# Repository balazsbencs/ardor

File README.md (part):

<h1 align="center">
  
</h1>

Ardor is a standalone Raspberry Pi guitar-processing platform with a realtime
audio engine, touchscreen/footswitch UI, preset storage, a browser-based manager
served by the device, and a reproducible Buildroot firmware image.

The signal chain supports Neural Amp Modeler `.nam` files, cabinet impulse
responses, 35 hosted modulation/delay/reverb effects, compression, noise
gating, five-band parametric EQ with high-pass and low-pass filters, global gain,
and a safety limiter. The same
LVGL interface runs in the SDL desktop simulator and on the Raspberry Pi Touch
Display 2.

Presets support serial chains, Dual Rig's separate left and right paths, and
Wet/Dry/Wet routing with a mono amp lane mixed alongside a stereo effects lane.

The pedal is an appliance rather than a plugin host. Plugin formats and an OTA
update workflow are outside the current scope.

<table>
  <tr>
    <td width="50%"></td>
    <td width="50%"></td>
  </tr>
  <tr>
    <td align="center"><sub>Build the chain from neural amps, cabs and effects</sub></td>
    <td align="center"><sub>Four-track looper on the footswitches</sub></td>
  </tr>
</table>

## What You Need

To build an Ardor pedal, start with a Raspberry Pi 4 (the 1 GB model is
enough), its USB-C power supply, and a microSD card for the Ardor image. Put
the Raspberry Pi Codec Zero audio board on top of the Pi, and connect the 5 inch
Raspberry Pi Touch Display 2 with its ribbon cable. A guitar cannot connect
directly to the Codec Zero, so you also need the small Ardor guitar input buffer
board. You can order it from JLCPCB with the parts already fitted (see
[Guitar Input Buffer](#guitar-input-buffer)), and it runs from a normal 9 V
guitar pedal power supply. For a complete floor pedal, add four momentary
footswitches, one rotary knob (encoder) for the master volume, one 1/4 inch
input jack, two 1/4 inch output jacks, and a case. You can 3D print the case
from [`enclosure.openscad`](enclosure.openscad). You need a soldering iron for
some basic soldering of the jacks, switches, and wires. MIDI and expression
pedal inputs come later. The [hardware assembly guide](docs/hardware-assembly.md)
shows all the wiring.

## Community

See [CONTRIBUTING.md](CONTRIBUTING.md) before proposing changes. Contributors
are recognized in [CONTRIBUTORS.md](CONTRIBUTORS.md), and suspected
vulnerabilities should be reported privately according to
[SECURITY.md](SECURITY.md).

## Requirements

- CMake 3.20+
- C++20 compiler
- Single-precision FFTW development files (`libfftw3-dev` on Debian/Ubuntu,
  `brew install fftw` on macOS). Custom SDK paths can be supplied through
  `ARDOR_FFTW_INCLUDE_DIR` and `ARDOR_FFTW_LIBRARY` at CMake configure.
- Git access during CMake configure, for `miniaudio` and `NeuralAmpModelerCore`
- SDL2 for the LVGL desktop simulator (`ARDOR_UI_BACKEND=sdl`)
- macOS for desktop testing, or Linux for target-style builds
- Optional: Go for the manager daemon, Node.js 24 via `nvm use` for the manager
  web app, and Docker for the Buildroot firmware image
- Local test assets:
  - `models/test.nam`
  - `irs/test.wav`
  - optional `reverb-irs/test.wav`
  - optional dry input WAV for offline rendering

Real `.nam` and IR files are ignored by git. Keep licensed/user-provided assets local unless redistribution is allowed.

The POG3 DSP links FFTW, which is GPL-2.0-or-later. Distribution of FFTW-linked
binaries must comply with that license; the repository's MIT license does not
cover FFTW. See [the FFT backend notes](docs/pog3-fft-backend-evaluation.md).

## Guitar Input Buffer

A passive guitar must pass through the Ardor input buffer before it reaches
the Codec Zero. The repository contains the separate, minimal KiCad project
in [`buffer/`](buffer/).

You can order a board with the SMD parts fitted through
[JLCPCB](https://jlcpcb.com/). Upload these files from
[`buffer/jlcpcb/production_files/`](buffer/jlcpcb/production_files/):

- [`GERBER-buffer.zip`](buffer/jlcpcb/production_files/GERBER-buffer.zip) for the PCB files.
- [`BOM-buffer.csv`](buffer/jlcpcb/production_files/BOM-buffer.csv) for the parts list.
- [`CPL-buffer.csv`](buffer/jlcpcb/production_files/CPL-buffer.csv) for the part placement list.

The production files do not include audio jacks, wires, connectors, or the
enclosure. Add these parts after the board arrives. Connect the guitar jack to
`GUITAR_IN` and connect `GUITAR_OUT` to the Codec Zero input. Follow the buffer
schematic for power and ground connections.

## Preset Storage

Preset files live under the data root in bank/slot folders, for example:

- `presets/bank-000/preset-0.json`

Block assets inside preset JSON stay relative to that same data root, such as `models/clean.nam`, `irs/open-back.wav`, or `reverb-irs/small-room.wav`. Cabinet IRs and convolution reverb IRs use separate directories. Existing convolution presets that reference an installed `irs/` asset remain compatible, while new reverb selections use `reverb-irs/`. Absolute paths and `..` traversal are rejected. Real `.nam` models and IRs stay local and are not committed unless redistribution is allowed.

Convolution reverb exposes **Reverb time** in the pedal and manager editors.
It scales the recorded decay from 25% to 100%; 100% preserves the original IR.
For example, a two-second decay becomes approximately one second at 50%.
The processor estimates RT60 from the loaded stereo IR and applies a decay
envelope without changing reflection timing, pitch, or embedded pre-delay.
IRs shorter than 100 ms, silent impulses, and responses without a reliable
decay estimate stay unchanged. The four-second IR cap still applies.
Live edits crossfade using the existing convolution history. This control is
shared across scenes; convolution-kernel preparation runs on the control thread.

### Scenes

Version-4 presets contain four named scenes. A scene changes prepared parameter
values, qualified effect bypass states, input gain, WDW lane values, and a
post-rig trim without rebuilding the audio engine. Each scene can switch
instantly or transition over 0.1–10 seconds.

On a scene-enabled preset, hold FS3 + FS4 for 600 ms to enter or leave the
Scenes layer. The four footswitches then recall the four scene plates. Hold
FS1 + FS2 for one second to open the muted tuner. The touchscreen and Manager
show the live scene separately from the scene being edited.

Qualified delay and reverb blocks offer shared **Cut** and **Let ring** bypass
policies. Let ring stops new wet input while the existing decay continues for a
bounded lifetime. Version-4 data survives preset copies, backup/restore, hosted
read/write, and Looper source snapshots. Explicit flattening resolves one scene,
folds its trim into output gain, removes scene-only mappings, and produces the
minimum compatible ordinary preset version. See
[`presets/bank-002/preset-1.json`](presets/bank-002/preset-1.json) for an
asset-free example.

### Supported Parameters

Preset globals:

- `global.inputGainDb`: input gain before NAM.
- `global.outputGainDb`: output gain after cab.
- `global.safetyLimitDb`: limiter ceiling, where `-1.0` is the default. Stored and applied, but not editable from the UI — it is a protective clipper, not a tone control.

NAM block params:

- `params.inputMode`: stereo-to-mono routing at the NAM input: `"sum"` averages left and right (default), `"left"` uses the left/mono channel, and `"right"` uses the right channel.
- `params.useNano`: when `true`, selects the embedded nano submodel to reduce CPU usage; missing or `false` selects the full model.

Pass `--input-reference-dbu DBU` to map the audio interface's measured analog
input reference to NAM models that contain `input_level_dbu` metadata. The
reference is the analog dBu RMS level that produces a 0 dBFS-peak 1 kHz sine at
the ADC. Models without the metadata retain unity input scaling. Preset input
gain remains available as a separate creative or corrective control.

Cab block params:

- `params.levelDb`: cab level before output gain.
- `params.mix`: `0.0` dry after-NAM signal, `1.0` full cab signal.

Dual Amp is one draggable `type: "dualAmp"` block with two fixed parallel
lanes. Both lanes receive the selected mono input; the left NAM → IR lane feeds
only the left output and the right NAM → IR lane feeds only the right output.
It uses:

- `params.inputMode`: `"sum"` (default), `"left"`, or `"right"`.
- `params.leftNamAsset` / `params.rightNamAsset`: relative `.nam` asset paths.
- `params.leftIrAsset` / `params.rightIrAsset`: relative IR asset paths.
- `params.leftUseNano` / `params.rightUseNano`: per-model nano selection.
- `params.leftCabLevelDb` / `params.rightCabLevelDb`: `-60..12` dB.
- `params.leftCabMix` / `params.rightCabMix`: `0.0..1.0`.
- `params.leftPolarityInvert` / `params.rightPolarityInvert`: whole-lane polarity.

An enabled Dual Amp block cannot be combined with standalone NAM or cabinet
blocks in the same preset. Existing version-1 serial presets remain compatible.

Dual Rig generalizes that fixed block to two independent child chains. It is a
version-2 preset block and remains one draggable item in the outer chain:

```json
{
  "version": 2,
  "blocks": [{
    "id": "rig-1",
    "type": "dualRig",
    "enabled": true,
    "asset": "",
    "params": {
      "inputMode": "sum",
      "leftLevelDb": 0,
      "leftPolarityInvert": false,
      "rightLevelDb": 0,
      "rightPolarityInvert": false
    },
    "lanes": {
      "left": { "blocks": [
        {"id":"left-nam","type":"nam","enabled":true,"asset":"models/clean.nam","params":{}},
        {"id":"left-cab","type":"cab","enabled":true,"asset":"irs/open.wav","params":{}},
        {"id":"left-chorus","type":"mod","enabled":true,"asset":"","params":{"mode":"chorus"}}
      ]},
      "right": { "blocks": [
        {"id":"right-nam","type":"nam","enabled":true,"asset":"models/crunch.nam","params":{}},
        {"id":"right-cab","type":"cab","enabled":true,"asset":"irs/closed.wav","params":{}},
        {"id":"right-delay","type":"delay","enabled":true,"asset":"","params":{"mode":"digital"}}
      ]}
    }
  }]
}
```

Both lanes receive the same selected mono input. Each lane is processed in its
declared order; the left lane's left output and the right lane's right output
are retained at the fixed merge. Child block IDs are globally unique, both
lanes must be non-empty, and split blocks cannot be nested. Version-1 presets
and the fixed `dualAmp` block remain supported.

Set the Dual Rig block's **Join** to **Mono Sum** to blend two NAM lanes, each
with an optional cabinet. Ardor folds each lane to mono, aligns their reported
latencies, applies lane level and polarity, and averages the two contributions.
The joined signal is identical on both channels. Stereo effects after the join
can still create stereo output. The preset stores `params.join: "monoSum"`.
When the field is absent, the join defaults to Stereo.

### Wet/Dry/Wet routing

Wet/Dry/Wet (WDW) routing splits the mono guitar input into two processed
chains and mixes them to stereo. Both lanes have their own Neural Amp Modeler
(NAM) block. The **Dry** lane is a mono amp path that can include drive and
tone processing; its output can be panned. The **Wet** lane is an amp path with
stereo modulation, delay, and reverb; its output width is adjustable. “Dry”
means the lane without stereo time effects, not an unprocessed guitar signal.
There is no raw-input bypass lane.

Each lane requires exactly one enabled NAM block and may have one cabinet IR
after the NAM. A separate cab is optional when the NAM capture already
contains its cabinet response. The Dry lane admits dynamics, EQ, distortion,
and wah blocks. The Wet lane admits modulation, delay, reverb, and stereo
blocks. A lane can be switched off or adjusted from −60 to +12 dB; Dry also
has pan, and Wet has width. Each lane supports up to ten blocks.

WDW is a separate preset topology from Dual Rig: Dual Rig sends its left and
right lanes to separate output channels, while WDW combines a mono Dry
contribution with a stereo Wet contribution. Choose Wet/Dry/Wet in the
preset's routing controls, then edit blocks in the Dry and Wet lanes. The
Manager exposes the topology under **Global → Topology**. See the
[Wet/Dry/Wet guide](website/src/pages/docs/wet-dry-wet.astro) for the editor
workflow and examples.

WDW presets use version 3 (or version 4 when scenes are enabled),
`routing: "wdw"`, and explicit `wdw.dry` and `wdw.wet` lane objects. The
top-level `blocks` array is empty. Both lanes share the preset's global input
gain, output gain, and safety limit. Scenes can change either lane's enabled
state and mix controls without rebuilding the audio engine.

Daisy effect blocks use no asset path and store catalog-defined normalized
`0.0..1.0` parameters. The built-in catalog currently contains 35 modes:

- 13 modulation/special effects: chorus, flanger, rotary, vibe, phaser,
  vintage/pattern tremolo, poly octave, auto swell, filter, formant,
  quadrature, and destroyer.
- 10 delays: digital, tape, dual, filter, lo-fi, bucket-brigade, duck,
  pattern, swell, and tremolo.
- 12 reverbs: room, hall, plate, spring, bloom, cloud, shimmer, chorale,
  nonlinear, swell, magneto, and reflections.

Each mode uses semantic labels, physical-value formatting, defaults, and
discrete choices from `src/daisyfx/DaisyFxCatalog.cpp`. Compressor blocks use
`type: "dynamics"` with mode `compressor`.

Noise Gate blocks use `type: "dynamics"` with mode `noise_gate`. Their numeric
parameters are `threshold_db`, `reduction_db`, `attack_ms`, `hold_ms`,
`release_ms`, `hysteresis_db`, and `sidechain_hpf_hz`. Detection is
stereo-linked and the gate adds no lookahead latency.

The Ardor-maintained Daisy effect engine lives under `src/daisyfx/hosted/`.
Its upstream origin and license are preserved there; host adaptation and effect
implementation now live together under `src/daisyfx/`.

Five-band EQ blocks use `type: "eq"`, mode `parametric_eq_5`, and five entries
in `params.bands`. Each band stores `enabled`, `frequency_hz` (20–20,000 Hz),
`q` (0.1–18), and `gain_db` (-18 to +18 dB). Missing fields receive indexed
band defaults; saved presets always contain exactly five complete bands. The
surrounding `high_pass` and `low_pass` filters store `enabled`, `frequency_hz`,
`q`, and `slope_db_per_octave` (6, 12, 18, or 24; default 12).

## Build

Desktop build with the SDL UI:

```sh
cmake -S . -B build-sdl -DARDOR_UI_BACKEND=sdl -DCMAKE_BUILD_TYPE=Release
cmake --build build-sdl -j
```

Primary executables include:

- `build-sdl/pedal-poc` — offline/realtime engine and integrated UI
- `build-sdl/pedal-ui-sim` — desktop-only LVGL simulator
- `build-sdl/audio-probe` — audio-device probe

An opt-in standalone desktop application is being developed for Mac first.
Configure with `-DARDOR_BUILD_DESKTOP=ON` and the SDL backend to build
`ardor-desktop` (`Ardor.app` on Mac). See the
[desktop prototype instructions](apps/ardor-desktop/README.md) for audio setup,
user-library storage, validation, and current limitations.

The full-chain [Ardor CLAP plugin](plugins/ardor-clap/README.md) is built with
`-DARDOR_BUILD_CLAP_PLUGIN=ON`. It includes the shared Ardor editor on Mac and
Windows with `-DARDOR_UI_BACKEND=memory`; Linux uses host-generated controls.
It supports host sample-rate conversion and per-project full-chain state, and
is separate from the Whammy plugin. Versioned Mac, Windows and Linux packages
are included in the main GitHub release.

The [standalone NAM loader](plugins/nam-clap/README.md) provides a smaller CLAP
effect for macOS Apple Silicon, with a native editor for the model's own controls
and selectable Nano/Standard tiers when exported together. Build it separately
with `cmake -S plugins/nam-clap -B build-nam-clap -DCMAKE_BUILD_TYPE=Release`.
Versioned Mac and Linux NAM packages are also included in the main release.
CI builds and validates both CLAP modules and checks all release packages before
publishing them alongside firmware.

For a headless build, configure with `-DARDOR_UI_BACKEND=none`. The Pi firmware
uses the `fbdev` backend through the Buildroot package.

## Test

```sh
ctest --test-dir build-sdl --output-on-failure
```

The CTest suite covers preset parsing and activation, realtime-chain behavior,
Daisy effects and automation, compressor, noise gate, parametric EQ, the
four-track looper and its persistent store, tuner and control gestures, UI
models/LVGL interaction, audio-device enumeration, and reload stress. The
looper timing benchmark is intentionally separate from CTest:

```sh
cmake --build build-sdl --target pedal-looper-bench
./build-sdl/pedal-looper-bench --block-sizes 64,128 --warmup 100 --iterations 1000
```

Host results are useful for regressions, but do not replace the Raspberry Pi 4
acceptance benchmark and ten-minute production-backend soak. Hardware latency,
Codec Zero routing, and subjective audio validation remain device-level checks.

## List Audio Devices

```sh
./build-sdl/pedal-poc --devices
```

On macOS with a Behringer U-Phoria UMC22, it usually appears as `USB Audio CODEC`.

## Offline Render

Preset files use relative asset paths under `--data-root`.

Preset-driven offline render:

```sh
./build-sdl/pedal-poc \
  --offline \
  --preset ./presets/bank-000/preset-0.json \
  --data-root . \
  --input ./dryguitar.wav \
  --output ./wet.wav
```

Bypass NAM and test only IR/output rendering:

```sh
./build-sdl/pedal-poc \
  --offline \
  --ir irs/test.wav \
  --input /path/to/dry-guitar.wav \
  --output /tmp/ardor-wet.wav \
  --bypass-nam
```

Run NAM plus IR:

```sh
./build-sdl/pedal-poc \
  --offline \
  --model models/test.nam \
  --ir irs/test.wav \
  --input /path/to/dry-guitar.wav \
  --output /tmp/ardor-wet.wav
```

Input and IR WAV files must be 48 kHz.

## Realtime Run

List devices first:

```sh
./build-sdl/pedal-poc --devices
```

Example output:

```text
Playback devices:
  [1] USB Audio CODEC
Capture devices:
  [1] USB Audio CODEC
```

Run with explicit UMC22 routing:

```sh
./build-sdl/pedal-poc \
  --realtime \
  --model models/test.nam \
  --ir irs/test.wav \
  --sample-rate 48000 \
  --block-size 64 \
  --capture-device 1 \
  --playback-device 1 \
  --input-channel right \
  --output-channel both \
  --input-gain-db -12 \
  --output-gain-db -6 \
  --safety-limit-db -1
```

Preset-driven realtime run:

```sh
./build-sdl/pedal-poc \
  --realtime \
  --preset ./presets/bank-000/preset-0.json \
  --data-root . \
  --capture-device 1 \
  --playback-device 1 \
  --input-channel left \
  --output-channel both \
  --block-size 64 \
  --ir-samples 8192
```

Stop with `Ctrl-C`.

### Realtime preset slot switching

Slot-based realtime mode loads presets from `--data-root`:

```sh
./build-sdl/pedal-poc --realtime --data-root . --bank 0 --slot 0 \
  --capture-device 1 --playback-device 1 --input-channel left --output-channel both \
  --block-size 64 --ir-samples 8192
```

While it is running, type `0`, `1`, `2`, or `3`, then Enter, to switch presets in the current bank. The app reloads outside the audio callback, restarts the realtime device, and resumes telemetry.

Use `--input-channel left` for input 1 and `--input-channel right` for input 2. On the UMC22, the instrument input is commonly the right/second capture channel.

Realtime mode uses the full IR by default through partitioned convolution. Use `--ir-samples N` to cap long IRs when comparing performance or testing slower hardware.

The output safety limiter is on by default at `-1 dBFS`; adjust it with `--safety-limit-db DB` or disable it with `--no-safety-limit`.

If the sound is overloaded, reduce `--input-gain-db` first. That lowers the signal before NAM. If the amp character is right but the final output clips, reduce `--output-gain-db`.

Add `--clip-debug` to print interval peaks at the input-gain boundary, after every effect block, and immediately before the safety limiter. For example:

```text
levels input=-7.2dBFS nam:amp=1.4dBFS CLIP[38] ir:cab=-0.8dBFS output=-1.1dBFS limiter=[122] first=nam:amp
```

`CLIP[n]` counts frames above 0 dBFS during the interval, and `first=` identifies the earliest boundary that crossed full scale. This distinguishes signal-level overload from intentional NAM distortion: if `input` or `nam:...` is first, reduce input gain; if `ir:...` is first, reduce cabinet level; if only `output` or `limiter` is active, reduce output gain or master volume. The meter observes processor boundaries—it cannot label the intentional nonlinear distortion inside a NAM model as clipping.

With `--clip-debug --ui`, the touchscreen status bar shows the same diagnosis: red `CLIP` with the first stage and peak, amber `LIMIT` when only the safety limiter engages, or green `LEVEL OK`. It refreshes once per second.

Realtime status prints once per second:

```text
callbacks=28125 over=0 over%=0.00 max=0.41ms avg=0.23ms budget=1.33ms
```

`over` counts callbacks that took longer than the audio budget. For `--block-size 64` at 48 kHz, the callback budget is about `1.33 ms`.

Dual Amp and Dual Rig always have a sequential fallback: the callback processes
the complete left lane and then the complete right lane. On a four-core Pi,
enable the optimized path with
`--parallel-rigs --audio-cpu 2 --rig-worker-cpu 3`. This keeps the callback at
`SCHED_FIFO/70` on CPU 2 and runs a persistent right-lane worker at
`SCHED_FIFO/69` on CPU 3; the callback processes the complete left lane
concurrently and joins the worker once at the fixed merge. Effects before and
after the parallel block still run serially on the callback thread. The two CPU
arguments are required and must differ. If the worker cannot obtain its
requested realtime policy or affinity, the rig reports the failure and uses
sequential processing. The older `--parallel-dual-amp` and
`--dual-amp-worker-cpu` spellings remain accepted.

The Buildroot image enables that layout by default through
`PARALLEL_RIGS=1`, `AUDIO_CPU=2`, and `RIG_WORKER_CPU=3` in
`/etc/ardor-pedal.env`. WDW adds two independent lane workers; the image
defaults to `WDW_DRY_WORKER_CPU=0` and `WDW_WET_WORKER_CPU=1` and passes them as
`--wdw-dry-worker-cpu` / `--wdw-wet-worker-cpu`. These assignments keep the
audio callback, legacy dual-rig worker, and both WDW lanes on distinct Pi 4
cores. The UI and non-audio work remain normal-priority Linux tasks; the
realtime DSP threads preempt them on their assigned cores.

Measure that layout on a running pedal over SSH:

```sh
./scripts/measure-device-performance.sh --duration 30 192.168.88.17
```

The probe reports whole-core utilization and headroom, per-thread CPU usage,
last CPU, affinity, realtime policy and priority, migrations, temperature, and
CPU clock range. Production builds also publish an atomic snapshot at
`/run/ardor-pedal.telemetry`; the probe uses its before/after counters to check
callback overruns, scheduling gaps, parallel-worker deadline misses,
non-finite DSP blocks, block-size mismatches, and overload bypass. It checks
that the callback is `SCHED_FIFO/70` on CPU 2. With a Dual Amp or Dual Rig
preset active, require and validate the `SCHED_FIFO/69` worker on CPU 3:

```sh
./scripts/measure-device-performance.sh \
  --duration 60 --require-worker 192.168.88.17
```

The local wrapper streams
`scripts/device-performance-remote.sh` to BusyBox `sh`; it does not install
anything or modify the pedal. Use `ARDOR_PI_HOST`, `ARDOR_SSH_USER`, and
`ARDOR_SSH_OPTS` for repeatable lab configuration. Passwords are handled by
OpenSSH and are never stored by the scripts. The final pass/fail verdict covers
thread placement, realtime scheduling, and audio/DSP fault counters;
utilization, headroom, clock, and thermal values remain measurements to compare
between presets and builds.

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
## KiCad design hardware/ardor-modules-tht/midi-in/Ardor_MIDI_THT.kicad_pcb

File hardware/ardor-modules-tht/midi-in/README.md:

# Isolated MIDI input / 3.3 V UART / HAND ASSEMBLY

T1.1 compact hand-assembly PCB: 39 × 35 mm. **Unbuilt engineering prototype.**

The dense MIDI carrier is 39 × 35 mm, replacing the 58 × 42 mm outline. The net connections and connector pin assignments are unchanged; the ferrites and optocoupler use the Hestore selections described below. The native 3 mm MIDI-loop-to-logic clearance rule remains enabled, including filled copper. Mounting holes are at (3, 32) and (36, 3) mm from the top-left board corner.

Front and assembly labels show values/types, with connector IDs retained for wiring. Some labels are covered by fitted parts. The 1N4148, SMC TVS and two 100n capacitor labels use 0.8 mm text; other labels use 0.9 mm. Full references and ratings remain in the BOM.

The 3D views omit the custom TVS bodies; the complete embedded body/courtyard reservations are checked separately. Confirm enclosure, socket and cable access before fabrication. See [layout and sourcing notes](review/layout-notes.md). This remains an unbuilt engineering candidate.

[KiCad project](Ardor_MIDI_THT.kicad_pro) · [Manual BOM](BOM.csv) · [Schematic](review/schematic.pdf) · [Bare-board Gerbers](assembly/Ardor_MIDI_THT-Gerbers.zip)

Use a female five-pin DIN panel socket. Wire numbered DIN contact 4 to J202.1 and contact 5 to J202.2. Leave DIN 1/2/3 and shell unwired; insulate the socket shell. Bond the enclosure to J203.1. Do not treat MIDI contact 5 as ground. Fit **Everlight H11L1, Hestore 100.435.31**, standard DIP-6 with 7.62 mm row spacing. It replaces onsemi H11L1M without changing the pin connections, 5 V supply or 3.3 V output pull-up. Everlight's M option has 10.16 mm lead spacing and is not the selected package. A 6N138 is DIP-8 with a different output stage and is not a drop-in replacement.

D203/D204 are **Littelfuse SMDJ24CA**, the agreed pair of large hand-solderable **SMC / DO-214AB** TVS parts. FB201/FB202 now use **FERROCORE LCBB-601, Hestore 100.327.86**, 600 Ω at 100 MHz, 2 A, 0.1 Ω maximum DCR, in 0805. Their 1.6 × 1.8 mm pads extend beyond the 2.2 × 1.45 mm maximum body for iron access; use tweezers and flux. Fit all four SMD parts first. Both ferrites and the bidirectional CA TVS parts are nonpolar. All remaining parts are through-hole. The beads replace the former axial 800 Ω parts and have different RF behavior; bench-test cable/EMC performance. D202 remains DC Components 1.5KE6.8CA; the two higher-voltage SMDJ24CA positions must not be populated with that low-voltage part.

Supply 5 V / 10 mA and 3.3 V / 5 mA. Set the host UART to 31250 baud, 8-N-1. J101.4 is a 3.3 V output into the host RX input.

Commission: inspect DIP orientation and D201 band, verify 5 V at U201.6 and 3.3 V at the output pull-up, then verify idle UART HIGH. Send known MIDI notes and check UART timing and decoding. Test long cables and real transmitters because the axial protection parts have different capacitance/RF behavior. Functional ground-loop isolation is not safety isolation.

## Connector pin assignments

Directions are relative to this board. Standard header square pads identify pin 1. Read reference and pin numbers from the back silkscreen; mirrored CAD exports are labelled as back views.

### J202 — MIDI INPUT FROM DIN SOCKET

| Pin | Net | Direction | Connect to |
|---|---|---|---|
| 1 | MIDI_4 | MIDI INPUT | Female DIN socket numbered contact 4. |
| 2 | MIDI_5 | MIDI INPUT | Female DIN socket numbered contact 5. |

### J101 — POWER INPUT + UART OUTPUT TO HOST

| Pin | Net | Direction | Connect to |
|---|---|---|---|
| 1 | +5V | POWER INPUT | Positive output of the matching regulated supply. |
| 2 | +3V3 | POWER INPUT | Positive output of the matching regulated supply. |
| 3 | GND | GROUND | Host or cable ground / 0 V. |
| 4 | MIDI_RX | OUTPUT | Host UART RX input, 31250 baud, 8-N-1. Do not connect to host TX. |

### J203 — METAL CASE BOND + GROUND

| Pin | Net | Direction | Connect to |
|---|---|---|---|
| 1 | CHASSIS | BOND | Aluminium enclosure bonding point; insulate the MIDI DIN shell. |
| 2 | GND | GROUND | Host or cable ground / 0 V. |

## Assembly and files

Solder and inspect the two SMC TVS parts and both 0805 ferrites first, then fit low-profile axial parts, sockets/headers and radial capacitors. Match D201 band and IC orientation. H1/H2 are 2.2 mm nonplated M2 mounting holes, not electrical terminals. Check enclosure clearance and capacitor/socket height. T1.1 compacts the layouts; hole positions differ from T1 and M1.

Use the manual BOM and the bare-board Gerber/drill ZIP. There is no SMT assembly order. Front silkscreen shows component values/types; the front fabrication drawing shows package outlines and orientation; use the BOM for values. Back silk includes port functions and pin numbers. Native checks and package manifests are under `verification/`; they do not replace prototype measurements.

[Assembly accessories](assembly/accessories.csv) list sockets, shunts and panel items in addition to the PCB component BOM.

[Family guide](../README.md) · [Substitution sources](../SOURCES.md) · [Native validation](verification/validation.json)

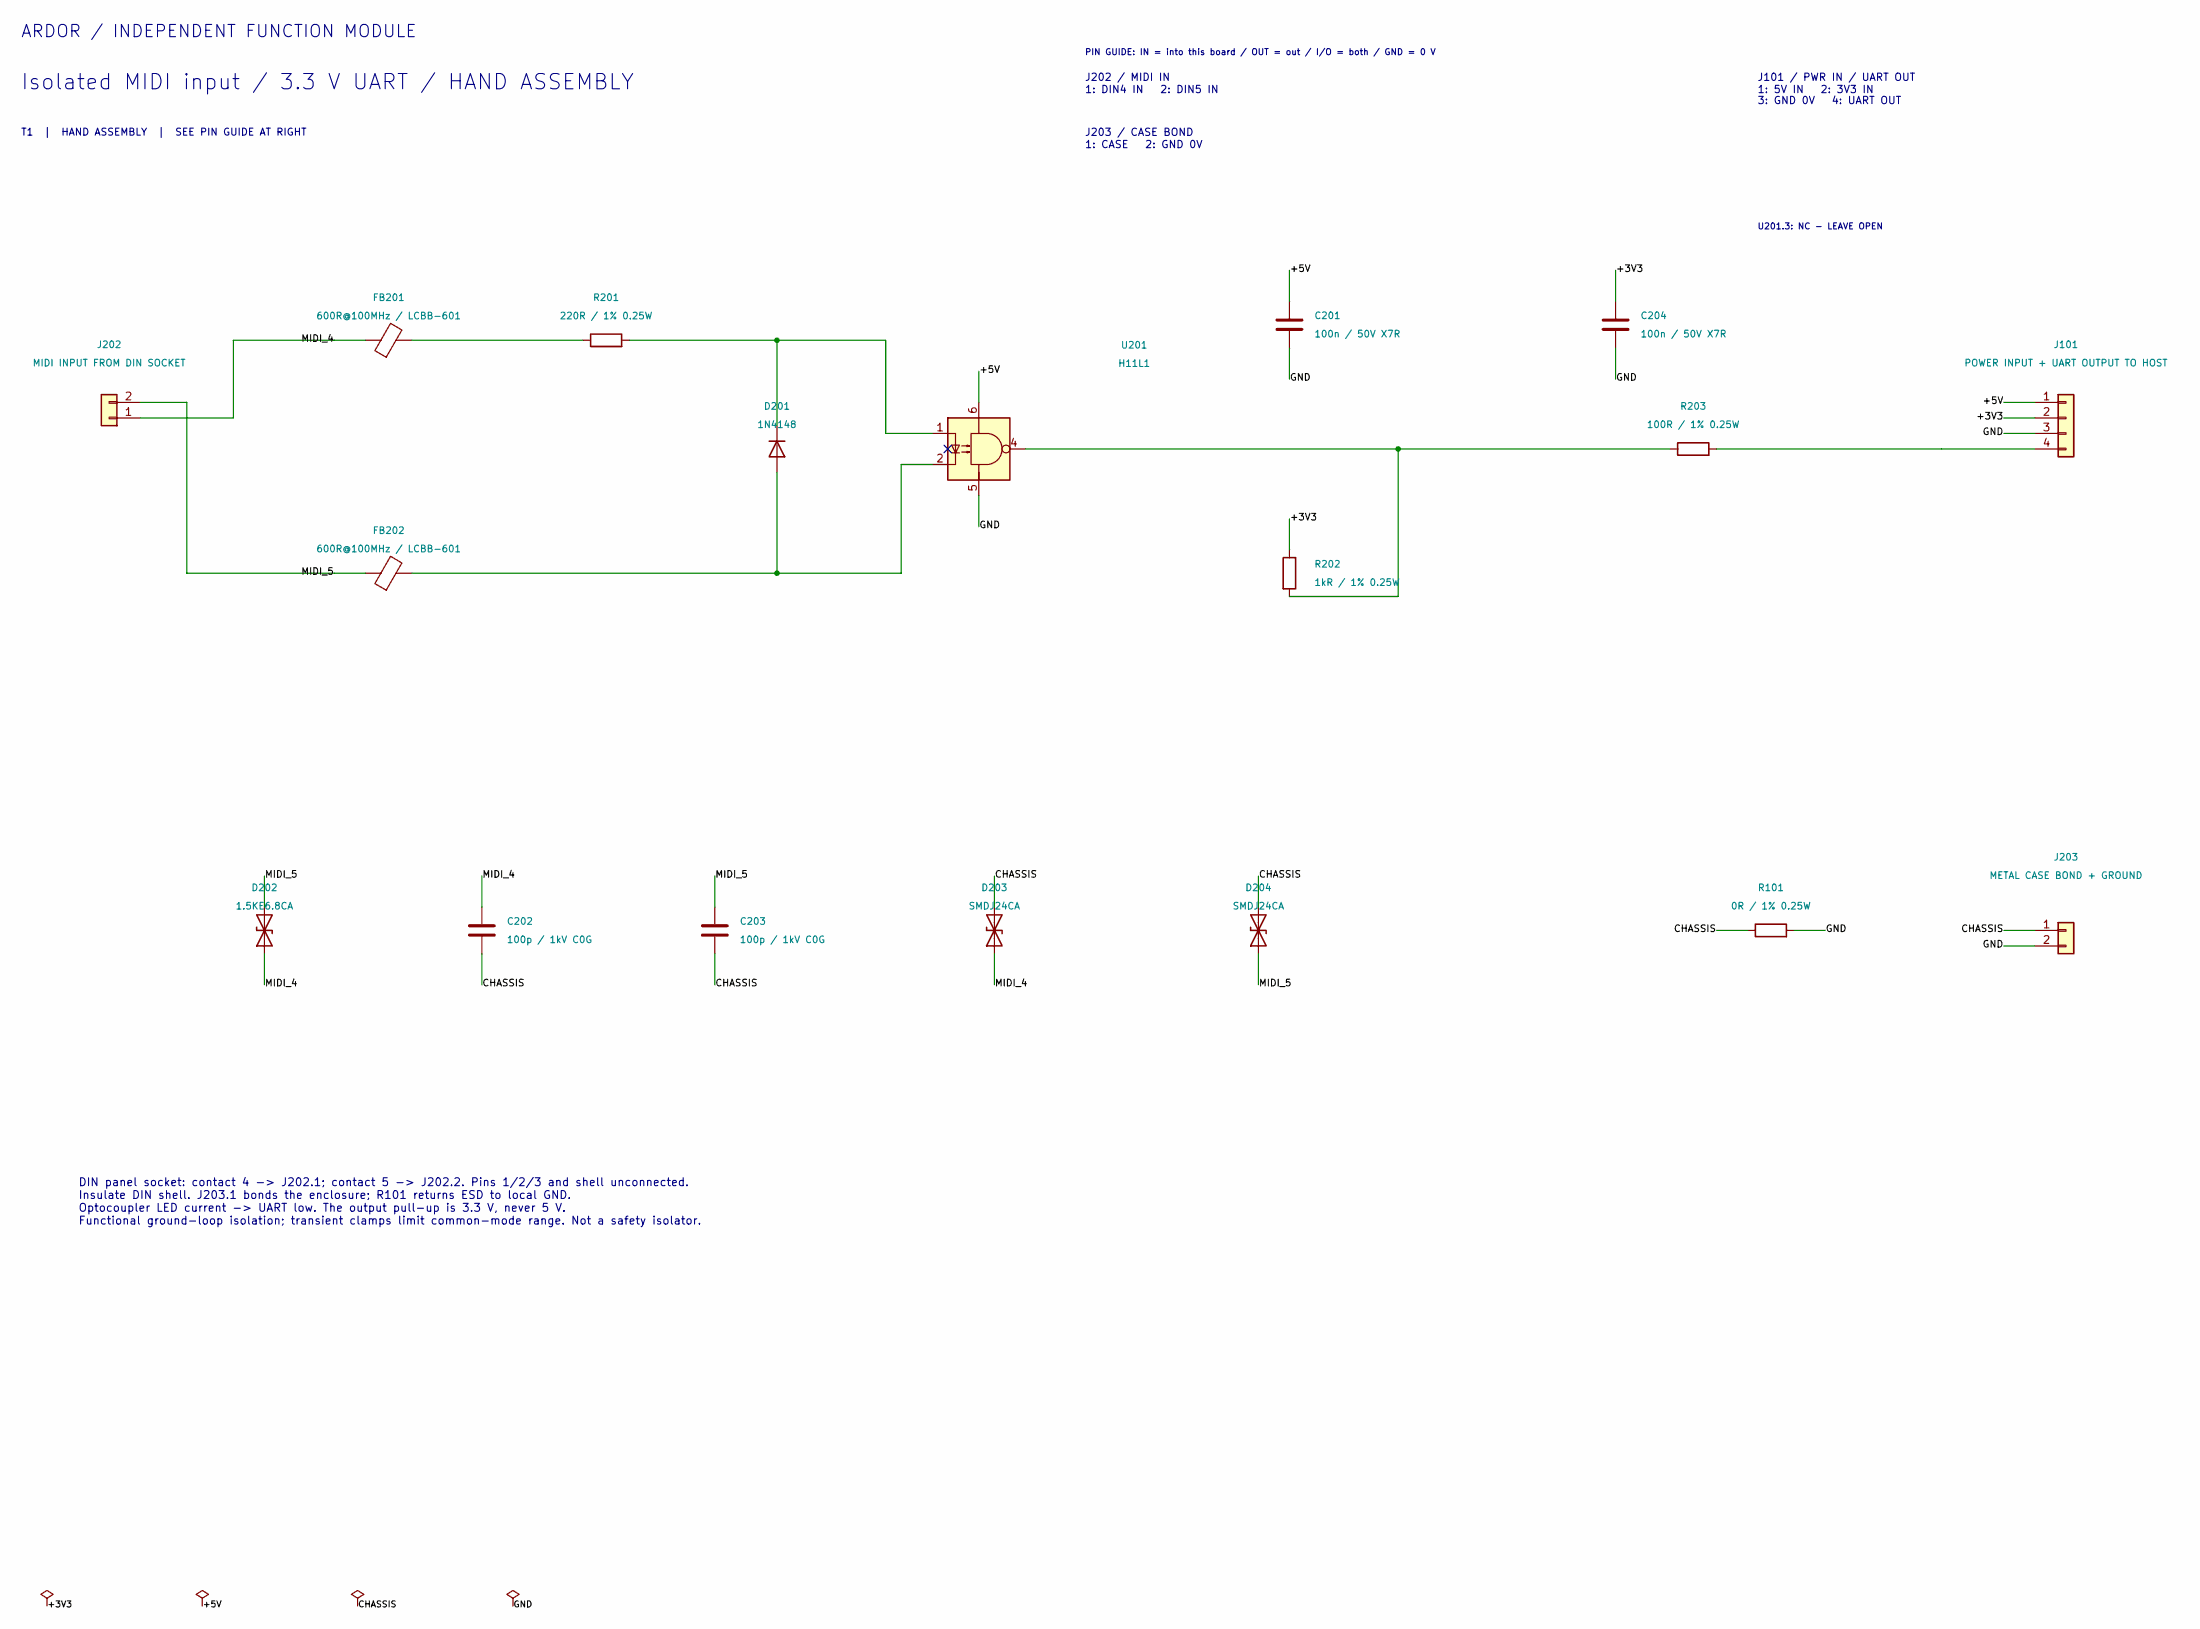
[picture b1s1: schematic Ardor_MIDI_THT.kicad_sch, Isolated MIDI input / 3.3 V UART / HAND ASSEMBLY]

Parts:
C201, C204: 100n / 50V X7R; C_Disc_D5.0mm_W2.5mm_P5.00mm; MPN 100nF 50V X7R radial, 5mm lead pitch
C202, C203: 100p / 1kV C0G; C_Disc_D5.0mm_W2.5mm_P5.00mm; MPN 100pF 1kV C0G disc, 5mm lead pitch
D201: 1N4148; D_DO-35_SOD27_P7.62mm_Horizontal; MPN Vishay 1N4148-TAP
D202: 1.5KE6.8CA; D_TVS_DC_1.5KE_P15.24mm; MPN DC Components 1.5KE6.8CA (HESTORE 100.4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
D203, D204: SMDJ24CA; D_SMC_Bidirectional_Handsolder; MPN Littelfuse SMDJ24CA (HESTORE 100.461.56)
FB201, FB202: 600R@100MHz / LCBB-601; FB_0805_Handsolder; MPN FERROCORE LCBB-601 (HESTORE 100.327.86)
J101: POWER INPUT + UART OUTPUT TO HOST; PinHeader_1x04_P2.54mm_Vertical; MPN PinHeader_1x04_P2.54mm_Vertical
J202: MIDI INPUT FROM DIN SOCKET; PinHeader_1x02_P2.54mm_Vertical; MPN PinHeader_1x02_P2.54mm_Vertical
J203: METAL CASE BOND + GROUND; PinHeader_1x02_P2.54mm_Vertical; MPN PinHeader_1x02_P2.54mm_Vertical
R101: 0R / 1% 0.25W; R_Axial_DIN0207_L6.3mm_D2.5mm_P10.16mm_Horizontal; MPN Axial metal film 0Ω 1% 0.25W
R201: 220R / 1% 0.25W; R_Axial_DIN0207_L6.3mm_D2.5mm_P10.16mm_Horizontal; MPN Axial metal film 220Ω 1% 0.25W
R202: 1kR / 1% 0.25W; R_Axial_DIN0207_L6.3mm_D2.5mm_P10.16mm_Horizontal; MPN Axial metal film 1kΩ 1% 0.25W
R203: 100R / 1% 0.25W; R_Axial_DIN0207_L6.3mm_D2.5mm_P10.16mm_Horizontal; MPN Axial metal film 100Ω 1% 0.25W
U201: H11L1; DIP-6_W7.62mm; MPN Everlight H11L1 (HESTORE 100.435.31)

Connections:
/+3V3: C204.1, J101.2, R202.1
/+5V: C201.1, J101.1, U201.6
/CHASSIS: C202.2, C203.2, D203.2 (A2), D204.2 (A2), J203.1, R101.1
/GND: C201.2, C204.2, J101.3, J203.2, R101.2, U201.5
/MIDI_4: C202.1, D202.1 (A1), D203.1 (A1), FB201.1, J202.1
/MIDI_5: C203.1, D202.2 (A2), D204.1 (A1), FB202.1, J202.2
unnamed: D201.2 (A), FB202.2, U201.2
unnamed: D201.1 (K), R201.2, U201.1
unnamed: FB201.2, R201.1
unnamed: J101.4, R203.2
unnamed: R202.2, R203.1, U201.4

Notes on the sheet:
ARDOR / INDEPENDENT FUNCTION MODULE
Isolated MIDI input / 3.3 V UART / HAND ASSEMBLY
T1 | HAND ASSEMBLY | SEE PIN GUIDE AT RIGHT
DIN panel socket: contact 4 -> J202.1; contact 5 -> J202.2. Pins 1/2/3 and shell unconnected. Insulate DIN shell. J203.1 bonds the enclosure; R101 returns ESD to local GND. Optocoupler LED current -> UART low. The output pull-up is 3.3 V, never 5 V. Functional ground-loop isolation; transient clamp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
PIN GUIDE: IN = into this board / OUT = out / I/O = both / GND = 0 V
J202 / MIDI IN
1: DIN4 IN 2: DIN5 IN
J101 / PWR IN / UART OUT
1: 5V IN 2: 3V3 IN
3: GND 0V 4: UART OUT
J203 / CASE BOND
1: CASE 2: GND 0V
U201.3: NC - LEAVE OPEN

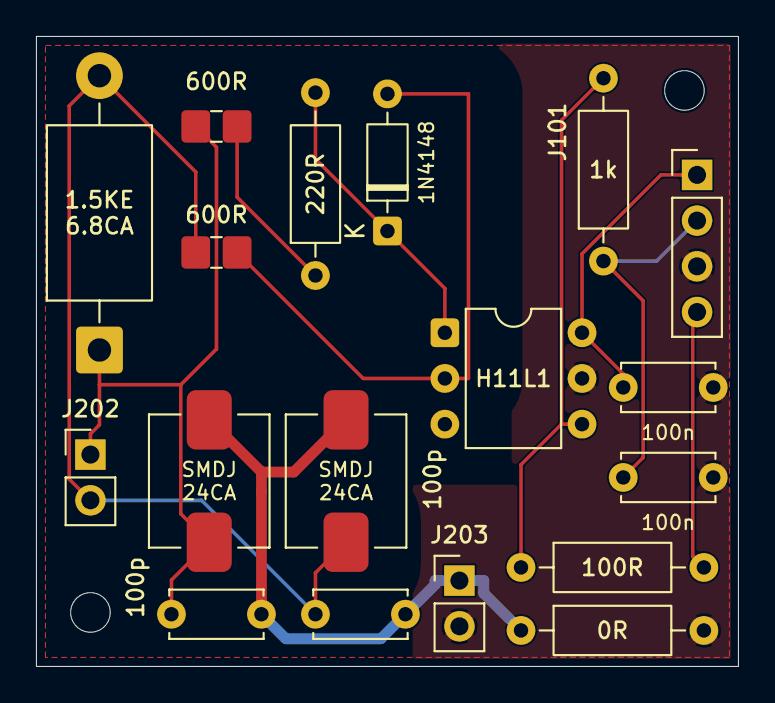
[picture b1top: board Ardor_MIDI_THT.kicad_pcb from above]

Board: 2 copper layers, 39.0 x 35.0 mm, 20 parts (0 on the bottom side), 11 nets.

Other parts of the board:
H1, H2: MountingHole_2.2mm_M2

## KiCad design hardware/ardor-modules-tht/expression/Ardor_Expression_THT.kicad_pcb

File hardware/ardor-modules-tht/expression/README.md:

# Passive expression pedal / I2C ADC / HAND ASSEMBLY

T1.1 compact hand-assembly PCB: 56 × 44 mm. **Unbuilt engineering prototype.**

The denser expression layout reduces the previous 72 × 50 mm carrier to 56 × 44 mm (31.6% less area), with the same circuit, components and pin assignments. Mounting holes are now at (3, 41) and (53, 3) mm from the top-left board corner. All axial parts lie flat; the complete ADC body remains reserved.

Front labels show component values or types instead of reference IDs; connector IDs still link to the complete back pin maps. Each pair of BAT85S clamp diodes shares one label between its two bodies. Some labels are inside component outlines and are covered after assembly. Clamp labels use 0.8 mm text; other labels use 0.9 mm. Electrical references and full ratings remain in the unchanged BOM.

The 3D views omit the custom ADS1115-M, TVS and ferrite bodies; their full embedded courtyards are checked separately. Confirm enclosure, socket and shunt heights before fabrication. This is an unbuilt layout candidate, not a production release.

[KiCad project](Ardor_Expression_THT.kicad_pro) · [Manual BOM](BOM.csv) · [Schematic](review/schematic.pdf) · [Bare-board Gerbers](assembly/Ardor_Expression_THT-Gerbers.zip)

Fit the **Hestore ADS1115-M, item 100.417.98**, using one **ten-pin 2.54 mm female socket** and a matching straight male header on the module. With the component side up, its 27.5 × 17 mm body lies above the header row inside the printed outline. The left-to-right order is **VDD, GND, SCL, SDA, ADDR, ALRT, A0, A1, A2, A3**. VDD is the square carrier pad (logical U301 pad 8), at the left end. See the [breakout pin translation](../SOURCES.md#ads1115-breakout-pin-translation). Do not rotate it 180 degrees. Adafruit and ADS1115-M2MINI boards do not match this footprint.

The purchased breakout already contains all small SMD parts. Only its ordinary header pins require soldering. ALRT is not wired; A2/A3 connect to ground. The module has an onboard 10 kΩ ADDR pull-down. JP302 must have one shunt: 1–2 selects 0x48, 2–3 selects 0x49; HIGH sources about 0.33 mA through the pull-down. No onboard resistor removal is required. ADS1115 registers/channels/addresses stay the same as M1.

The supplier schematic labels its chip ADS1015 while the product is sold as 16-bit ADS1115. Before relying on the expected ADC resolution, confirm the actual supplied chip/module. At the driver's 128 SPS ADS1115 setting, check single-shot conversion busy time near 7.8 ms; an ADS1015 at the corresponding data-rate bits runs near 0.625 ms. Check multiple known input voltages as well. A module containing ADS1015 fails the specified ADS1115 assembly requirement even if its I²C address responds.

Use a passive 10–100 kΩ expression pot; do not connect powered CV. JP301 needs **two** shunts: 1–3 plus 2–4 for tip wiper, or 3–5 plus 4–6 for ring wiper. TRS sleeve goes to J302.3. Change polarity with power off.

Leave **JP303 and JP304 unshunted initially**. The breakout has permanent onboard 10 kΩ SDA/SCL pull-ups; these jumpers control only the additional carrier 2.2 kΩ pair. With a Raspberry Pi's 1.8 kΩ pair, the effective resistance is approximately 1.53 kΩ before adding any other module. Add the carrier pair only after calculating total bus pull-up current and checking cable rise time. Removing the carrier shunts does not remove the breakout's pull-ups.

Supply 3.3 V / 15 mA. Commission without the breakout first: verify rail polarity at the socket, then fit the breakout and check I²C detection at 100 kHz. Select ±4.096 V PGA and 128 SPS, read AIN0 (wiper) and AIN1 (excitation reference), normalize AIN0/AIN1, calibrate endpoints and smooth. Test both polarity settings and open-cable behavior. Do not drive the pedal while the module is unpowered.

## Connector pin assignments

Directions are relative to this board. Standard header square pads identify pin 1. Read reference and pin numbers from the back silkscreen; mirrored CAD exports are labelled as back views.

### J302 — PASSIVE PEDAL INPUT / EXCITATION OUTPUT

| Pin | Net | Direction | Connect to |
|---|---|---|---|
| 1 | EXP_TIP | INPUT / OUTPUT | Passive expression socket tip; not a powered CV pedal. |
| 2 | EXP_RING | INPUT / OUTPUT | Passive expression socket ring; not a powered CV pedal. |
| 3 | GND | GROUND | TRS sleeve; pedal pot ground and enclosure bond. |

### J101 — 3V3 POWER INPUT + I2C TO HOST

| Pin | Net | Direction | Connect to |
|---|---|---|---|
| 1 | +3V3 | POWER INPUT | Positive output of the matching regulated supply. |
| 2 | GND | GROUND | Host or cable ground / 0 V. |
| 3 | SDA | INPUT / OUTPUT | Host I2C SDA data pin. |
| 4 | SCL | INPUT | Host I2C SCL clock pin. |

### JP301 — JUMPER ONLY: PEDAL POLARITY

| Pin | Net | Direction | Connect to |
|---|---|---|---|
| 1 | EXP_TIP | JUMPER | Fit a shunt to pin 3 for tip-wiper mode. |
| 2 | EXP_RING | JUMPER | Fit a shunt to pin 4 for tip-wiper mode. |
| 3 | EXP_WIPER | INPUT / JUMPER | Shunt 1-3 for tip wiper, or 3-5 for ring wiper. |
| 4 | EXP_EXC | OUTPUT / JUMPER | Shunt 2-4 for tip wiper, or 4-6 for ring wiper. |
| 5 | EXP_RING | JUMPER | Fit a shunt to pin 3 for ring-wiper mode. |
| 6 | EXP_TIP | JUMPER | Fit a shunt to pin 4 for ring-wiper mode. |

TIP: 1-3 + 2-4; RING: 3-5 + 4-6. Use TWO shunts; no external cable.

### JP302 — JUMPER ONLY: ADC ADDRESS

| Pin | Net | Direction | Connect to |
|---|---|---|---|
| 1 | GND | JUMPER | Shunt 1-2 selects address 0x48. |
| 2 | ADDR | CONTROL / JUMPER | Fit ONE shunt: 1-2 or 2-3. |
| 3 | +3V3_A | JUMPER | Shunt 2-3 selects address 0x49. |

1-2: 0x48; 2-3: 0x49. One shunt required; no external cable.

### JP303 — JUMPER ONLY: SDA PULLUP

| Pin | Net | Direction | Connect to |
|---|---|---|---|
| 1 | SDA_PULL | JUMPER | Shunt 1-2 only if the host has no SDA pull-up. |
| 2 | SDA | INPUT / OUTPUT / JUMPER | Same shunt; this is not a host cable connector. |

Fit 1-2 to enable. Remove if host already has a pull-up.

### JP304 — JUMPER ONLY: SCL PULLUP

| Pin | Net | Direction | Connect to |
|---|---|---|---|
| 1 | SCL_PULL | JUMPER | Shunt 1-2 only if the host has no SCL pull-up. |
| 2 | SCL | INPUT / JUMPER | Same shunt; this is not a host cable connector. |

Fit 1-2 to enable. Remove if host already has a pull-up.

## Assembly and files

Fit low-profile axial parts first, then sockets/headers and radial capacitors. Match diode bands, electrolytic polarity and IC notches to the PCB. Install the ICs or ADC breakout last. H1/H2 are 2.2 mm nonplated M2 mounting holes, not electrical terminals. Check enclosure clearance and capacitor/socket height. T1.1 compacts the layouts; hole positions differ from T1 and M1.

Use the manual BOM and the bare-board Gerber/drill ZIP. There is no SMT assembly order. Front silkscreen shows component values/types; the front fabrication drawing shows package outlines and orientation; use the BOM for values. Back silk includes port functions and pin numbers. Native checks and package manifests are under `verification/`; they do not replace prototype measurements.

[Assembly accessories](assembly/accessories.csv) list sockets, shunts and panel items in addition to the PCB component BOM.

[Family guide](../README.md) · [Substitution sources](../SOURCES.md) · [Native validation](verification/validation.json)

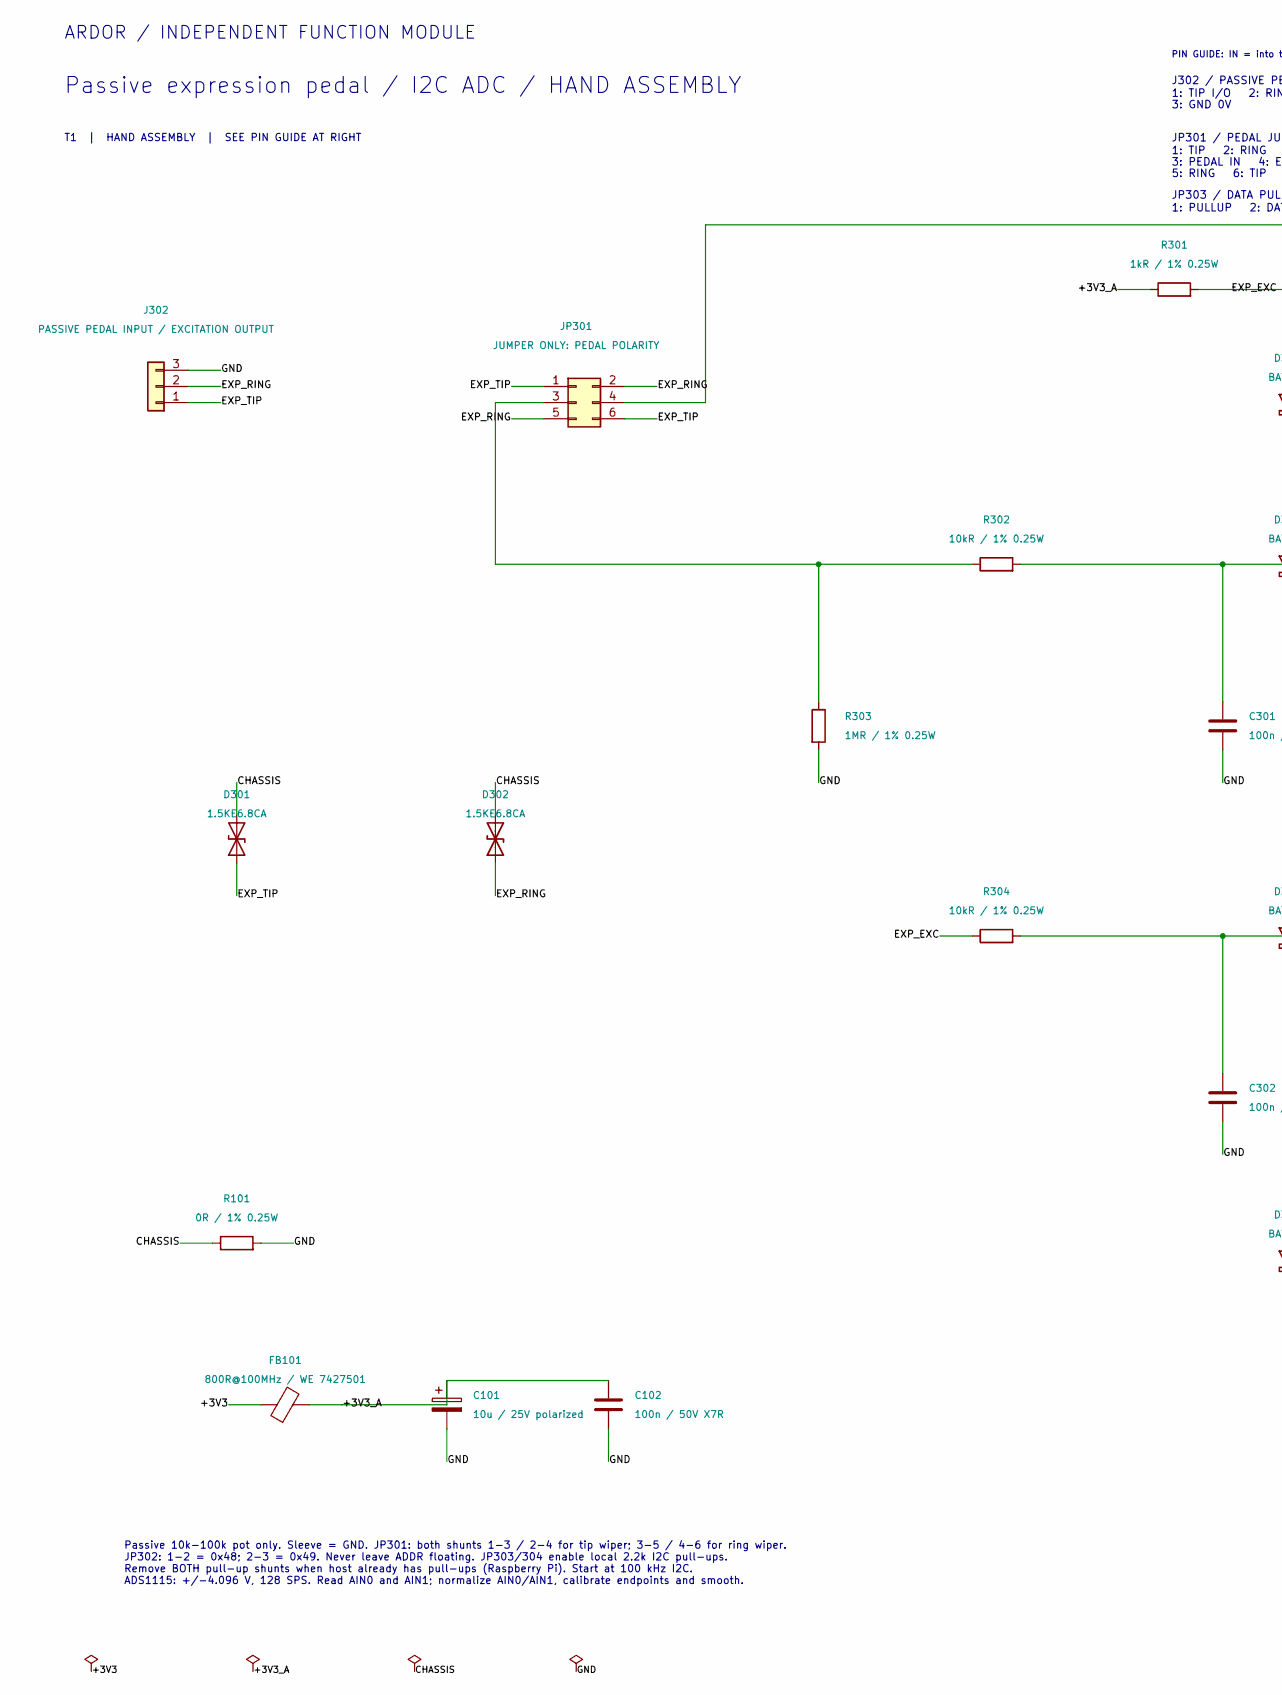
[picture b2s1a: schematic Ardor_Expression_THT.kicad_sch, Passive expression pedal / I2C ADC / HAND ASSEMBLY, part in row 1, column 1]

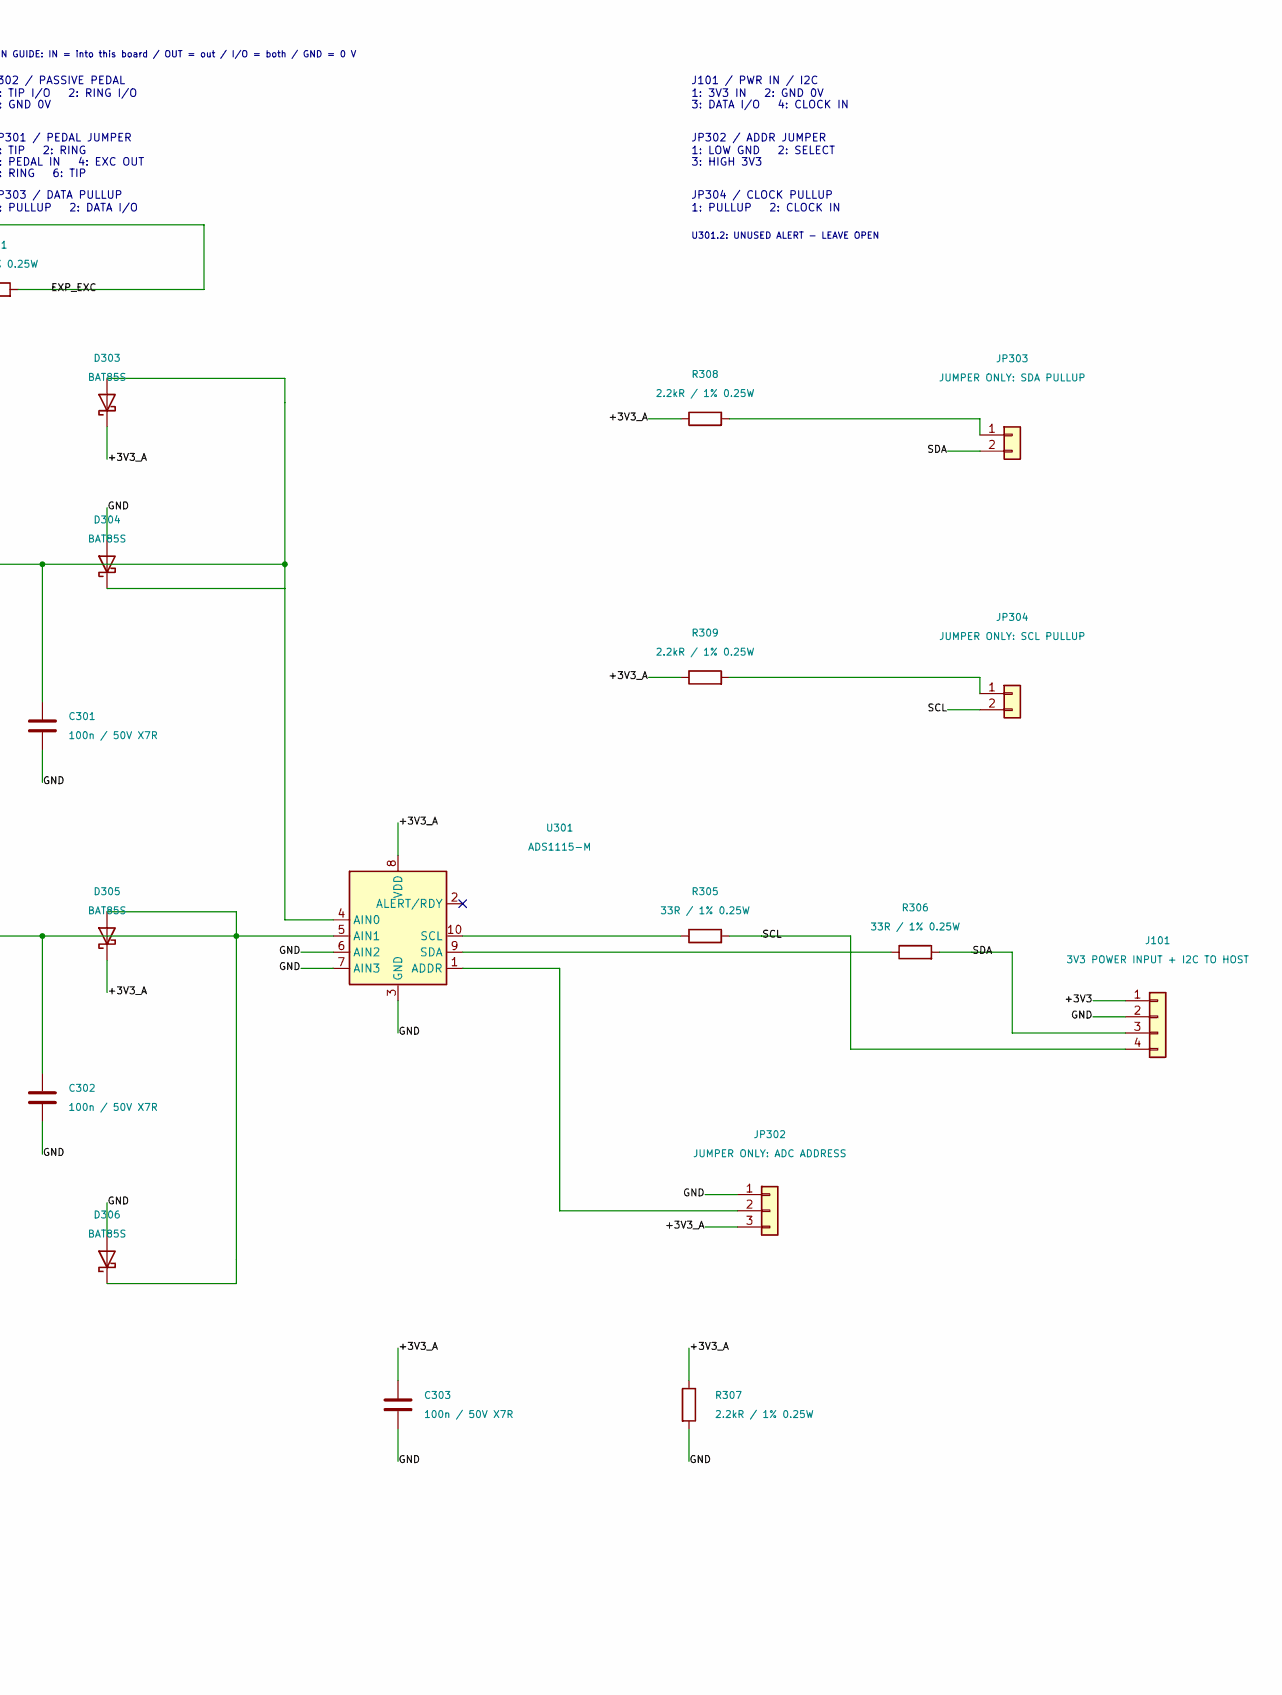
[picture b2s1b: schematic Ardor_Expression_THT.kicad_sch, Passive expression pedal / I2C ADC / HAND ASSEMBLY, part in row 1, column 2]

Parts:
C101: 10u / 25V polarized; CP_Radial_D6.3mm_P2.50mm; MPN Radial electrolytic 10uF 25V, D<=6.3mm 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
C102, C301, C302, C303: 100n / 50V X7R; C_Disc_D5.0mm_W2.5mm_P5.00mm; MPN 100nF 50V X7R radial, 5mm lead pitch
D301, D302: 1.5KE6.8CA; D_TVS_DC_1.5KE_P15.24mm; MPN DC Components 1.5KE6.8CA (HESTORE 100.4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
D303, D304, D305, D306: BAT85S; D_DO-35_SOD27_P7.62mm_Horizontal; MPN Vishay BAT85S-TAP
FB101: 800R@100MHz / WE 7427501; Ferrite_WE_7427501_P15.24mm; MPN Wurth Elektronik 7427501
J101: 3V3 POWER INPUT + I2C TO HOST; PinHeader_1x04_P2.54mm_Vertical; MPN PinHeader_1x04_P2.54mm_Vertical
J302: PASSIVE PEDAL INPUT / EXCITATION OUTPUT; PinHeader_1x03_P2.54mm_Vertical; MPN PinHeader_1x03_P2.54mm_Vertical
JP301: JUMPER ONLY: PEDAL POLARITY; PinHeader_2x03_P2.54mm_Vertical; MPN PinHeader_2x03_P2.54mm_Vertical
JP302: JUMPER ONLY: ADC ADDRESS; PinHeader_1x03_P2.54mm_Vertical; MPN PinHeader_1x03_P2.54mm_Vertical
JP303: JUMPER ONLY: SDA PULLUP; PinHeader_1x02_P2.54mm_Vertical; MPN PinHeader_1x02_P2.54mm_Vertical
JP304: JUMPER ONLY: SCL PULLUP; PinHeader_1x02_P2.54mm_Vertical; MPN PinHeader_1x02_P2.54mm_Vertical
R101: 0R / 1% 0.25W; R_Axial_DIN0207_L6.3mm_D2.5mm_P10.16mm_Horizontal; MPN Axial metal film 0Ω 1% 0.25W
R301: 1kR / 1% 0.25W; R_Axial_DIN0207_L6.3mm_D2.5mm_P10.16mm_Horizontal; MPN Axial metal film 1kΩ 1% 0.25W
R302, R304: 10kR / 1% 0.25W; R_Axial_DIN0207_L6.3mm_D2.5mm_P10.16mm_Horizontal; MPN Axial metal film 10kΩ 1% 0.25W
R303: 1MR / 1% 0.25W; R_Axial_DIN0207_L6.3mm_D2.5mm_P10.16mm_Horizontal; MPN Axial metal film 1MΩ 1% 0.25W
R305, R306: 33R / 1% 0.25W; R_Axial_DIN0207_L6.3mm_D2.5mm_P10.16mm_Horizontal; MPN Axial metal film 33Ω 1% 0.25W
R307, R308, R309: 2.2kR / 1% 0.25W; R_Axial_DIN0207_L6.3mm_D2.5mm_P10.16mm_Horizontal; MPN Axial metal film 2.2kΩ 1% 0.25W
U301: ADS1115-M; ADS1115_M_HESTORE_10041798; MPN ADS1115-M (HESTORE 100.417.98)

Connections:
/+3V3: FB101.1, J101.1
/+3V3_A: C101.1, C102.1, C303.1, D303.1 (K), D305.1 (K), FB101.2, JP302.3, R301.1, R307.1, R308.1, R309.1, U301.8 (VDD)
/CHASSIS: D301.2 (A2), D302.2 (A2), R101.1
/EXP_EXC: JP301.4, R301.2, R304.1
/EXP_RING: D302.1 (A1), J302.2, JP301.2, JP301.5
/EXP_TIP: D301.1 (A1), J302.1, JP301.1, JP301.6
/GND: C101.2, C102.2, C301.2, C302.2, C303.2, D304.2 (A), D306.2 (A), J101.2, J302.3, JP302.1, R101.2, R303.2, R307.2, U301.3 (GND), U301.6 (AIN2), U301.7 (AIN3)
/SCL: J101.4, JP304.2, R305.2
/SDA: J101.3, JP303.2, R306.2
unnamed: C301.1, D303.2 (A), D304.1 (K), R302.2, U301.4 (AIN0)
unnamed: C302.1, D305.2 (A), D306.1 (K), R304.2, U301.5 (AIN1)
unnamed: JP301.3, R302.1, R303.1
unnamed: JP302.2, U301.1 (ADDR)
unnamed: JP303.1, R308.2
unnamed: JP304.1, R309.2
unnamed: R305.1, U301.10 (SCL)
unnamed: R306.1, U301.9 (SDA)

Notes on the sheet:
ARDOR / INDEPENDENT FUNCTION MODULE
Passive expression pedal / I2C ADC / HAND ASSEMBLY
T1 | HAND ASSEMBLY | SEE PIN GUIDE AT RIGHT
Passive 10k-100k pot only. Sleeve = GND. JP301: both shunts 1-3 / 2-4 for tip wiper; 3-5 / 4-6 for ring wiper. JP302: 1-2 = 0x48; 2-3 = 0x49. Never leave ADDR floating. JP303/304 enable local 2.2k I2C pull-ups. Remove BOTH pull-up shunts when host already has pull-ups (Raspberry Pi). Start at 100 k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
PIN GUIDE: IN = into this board / OUT = out / I/O = both / GND = 0 V
J302 / PASSIVE PEDAL
1: TIP I/O 2: RING I/O
3: GND 0V
J101 / PWR IN / I2C
1: 3V3 IN 2: GND 0V
3: DATA I/O 4: CLOCK IN
JP301 / PEDAL JUMPER
1: TIP 2: RING
3: PEDAL IN 4: EXC OUT
5: RING 6: TIP
JP302 / ADDR JUMPER
1: LOW GND 2: SELECT
3: HIGH 3V3
JP303 / DATA PULLUP
1: PULLUP 2: DATA I/O
JP304 / CLOCK PULLUP
1: PULLUP 2: CLOCK IN
U301.2: UNUSED ALERT - LEAVE OPEN
